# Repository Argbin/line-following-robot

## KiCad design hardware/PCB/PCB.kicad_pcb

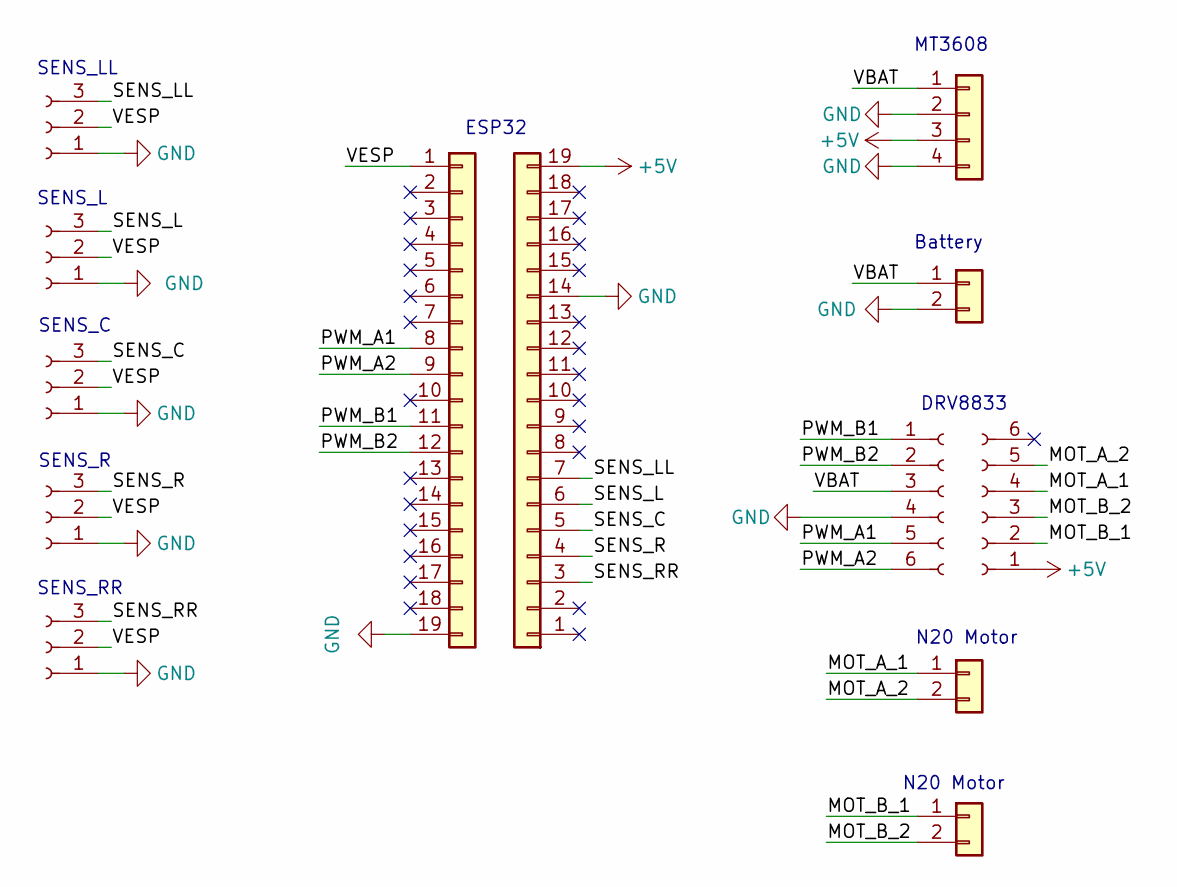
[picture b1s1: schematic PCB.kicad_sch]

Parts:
J1, J5, J6: Conn_01x02; TerminalBlock_Phoenix_MKDS-1,5-2-5.08_1x02_P5.08mm_Horizont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
J2: Conn_01x04; PinHeader_1x04_P2.54mm_Vertical
J3, J4: Conn_01x19; PinSocket_1x19_P2.54mm_Vertical
J7, J8, J11, J12, J13: Conn_01x03_Socket; PinHeader_1x03_P2.54mm_Vertical
J9, J10: Conn_01x06_Socket; PinSocket_1x06_P2.54mm_Vertical

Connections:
+5V: J2.3, J4.19, J10.1
/MOT_A_1: J5.1, J10.4
/MOT_A_2: J5.2, J10.5
/MOT_B_1: J6.1, J10.2
/MOT_B_2: J6.2, J10.3
/PWM_A1: J3.8, J9.5
/PWM_A2: J3.9, J9.6
/PWM_B1: J3.11, J9.1
/PWM_B2: J3.12, J9.2
/SENS_C: J4.5, J11.3
/SENS_L: J4.6, J8.3
/SENS_LL: J4.7, J7.3
/SENS_R: J4.4, J12.3
/SENS_RR: J4.3, J13.3
/VBAT: J1.1, J2.1, J9.3
/VESP: J3.1, J7.2, J8.2, J11.2, J12.2, J13.2
GND: J1.2, J2.2, J2.4, J3.19, J4.14, J7.1, J8.1, J9.4, J11.1, J12.1, J13.1

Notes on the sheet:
SENS_C
Battery
DRV8833
SENS_RR
ESP32
SENS_L
N20 Motor
MT3608
SENS_LL
SENS_R

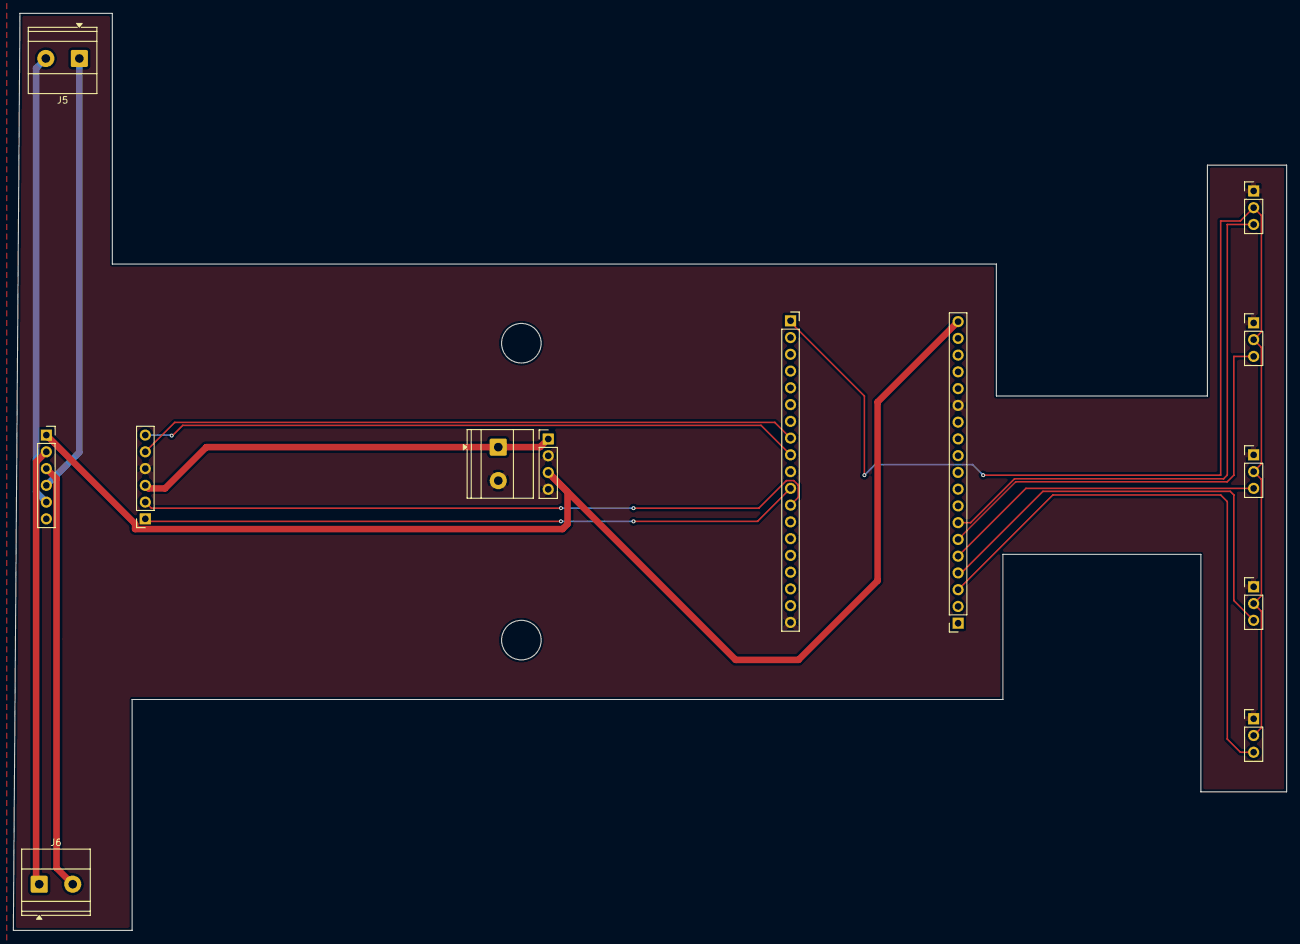
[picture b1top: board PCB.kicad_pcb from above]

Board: 2 copper layers, 193.0 x 139.0 mm, 13 parts (0 on the bottom side), 17 nets.

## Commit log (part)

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2026-03-25 Add .gitignore and code.ino file.
2026-05-26 Design a PCB in kiCad The dimentions for the motor driver might not be correct. May change when i am able to measure in real life.
2026-05-31 Update PCB design with correct measurements.
